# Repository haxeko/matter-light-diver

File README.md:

# matter-light-diver – Driver đèn CCT 3 dây, ESP32‑C6, Matter over Thread

Thiết kế hoàn chỉnh (tài liệu, sơ đồ nguyên lý, tính toán, floorplan PCB, BOM, firmware) cho **driver đèn LED điều chỉnh nhiệt độ màu loại 3 dây** (V+ chung, CW–, WW–) điều khiển bằng **ESP32‑C6** qua **Matter over Thread**, có **nguồn flyback cách ly** bên trong và **3 nút gạt chọn công suất**. Kiến trúc theo kiểu driver đèn thông minh thương mại: flyback CC/CV + MCU ở phía thứ cấp (SELV) + chuyển kênh CW/WW bằng PWM bù nhau.

| Thông số | Giá trị |
|---|---|
| Vào | 176–264 VAC |
| Ra | 20–42 V, 250–950 mA (8 mức DIP), 40 W max; bản 20 W cho PCB 30 × 60 mm |
| Điều khiển | Matter 1.x – Color Temperature Light, Thread FTD, commissioning BLE |
| Điều sáng | 1–100 % analog CC (12 bit), không nhấp nháy; CCT 2700–6500 K |
| Cách ly | tăng cường 3.75 kV, creepage ≥ 8 mm, opto 5 kV, tụ Y1 |
| PCB | KiCad 30 × 95 mm (40 W), 2 lớp, THT mặt trên / SMD mặt dưới; biến thể 30 × 60–65 mm (≤ 20 W) |

## Cấu trúc kho

```
docs/                      tài liệu thiết kế (tiếng Việt)
  01-tong-quan-kien-truc.md      yêu cầu, kiến trúc, bảng DIP
  02-nguon-cach-ly-flyback.md    tính toán flyback, biến áp, linh kiện sơ cấp
  03-thu-cap-cc-cv-dieu-sang.md  vòng CC/CV, PWM→DAC, chuyển kênh CW/WW, nguồn phụ
  04-mcu-esp32c6.md              GPIO, nạp/debug, anten
  05-pcb-layout.md               floorplan, khoảng cách an toàn, nhiệt
  06-firmware.md                 kiến trúc firmware, thuật toán, build, commissioning
  07-kiem-thu-an-toan.md         bring-up, kiểm thử, an toàn, EMC
  bom/BOM.csv                    danh mục linh kiện (có mã thay thế LCSC)
  images/block_diagram.svg       sơ đồ khối (sinh bởi gen_block_diagram.py)
hardware/
  kicad/                         DỰ ÁN KICAD (schematic + PCB 30x95 mm, Gerber, DSN) sinh từ design_db.py
  calc/flyback_calc.py           tính toán flyback (in bảng Markdown / JSON)
  calc/secondary_calc.py         bảng DIP, vòng CC, kẹp CV, MOSFET, nguồn phụ
  schematics/0X_*.svg            sơ đồ nguyên lý 7 khối (sinh bởi gen_0X_*.py, schemdraw)
  pcb/floorplan_30x90.svg        floorplan PCB (sinh bởi gen_floorplan.py)
firmware/                        dự án ESP-IDF 5.2 + esp-matter 1.3/1.4 (ESP32-C6)
  main/app_main.cpp              node Matter, endpoint 0x010C, OpenThread
  main/app_driver.cpp            LEDC/ADC/GPIO/nút/LED, tick 10 ms, bảo vệ
  main/light_engine.c            toán học điều sáng/CCT (thuần C)
  main/board_config.h            bản đồ chân, hằng số phần cứng
  test_host/                     unit test chạy bằng gcc
```

## Sơ đồ nguyên lý

| Khối | Tệp |
|---|---|
| 1 – Đầu vào AC, lọc EMI, chỉnh lưu | `hardware/schematics/01_input_filter.svg` |
| 2 – Flyback: T1 PQ20/20, Q1, clamp, cuộn phụ, chỉnh lưu thứ cấp | `02_flyback_stage.svg` |
| 3 – UCC28740, VS, HV start‑up, opto, tụ Y | `03_controller.svg` |
| 4 – Khuếch đại dòng, bộ lỗi CC, TL431 CV, tham chiếu PWM→DAC, ADC | `04_cc_cv_loop.svg` |
| 5 – Dịch mức, MOSFET CW/WW, shunt, đầu ra 3 dây | `05_output_switch.svg` |
| 6 – Buck 5 V, LDO 3.3 V | `06_aux_supply.svg` |
| 7 – ESP32‑C6‑MINI‑1, DIP, nút, LED, NTC, USB/UART | `07_mcu.svg` |

Sinh lại hình/tính toán (cần `pip install schemdraw`):

```bash
python3 hardware/calc/flyback_calc.py
python3 hardware/calc/secondary_calc.py
for f in hardware/schematics/gen_*.py docs/images/gen_block_diagram.py hardware/pcb/gen_floorplan.py; do python3 "$f"; done
```

## PCB KiCad

`hardware/kicad/` chứa project KiCad 7 (mở được bằng 7/8/9): `matter_cct_driver.kicad_pcb` (đặt linh kiện xong, đi dây tự động ≈ 70 % kết nối (160/230), phần đã đi sạch DRC; phần còn lại hoàn thiện tay hoặc Freerouting), schematic kết nối, thư viện footprint riêng (ESP32‑C6‑MINI‑1, PQ20/20, UU9.8…), Gerber/drill, PDF/SVG hai mặt và file DSN cho Freerouting. Toàn bộ được sinh từ `hardware/kicad/design_db.py` bằng API `pcbnew`; xem `hardware/kicad/README.md`.

## Firmware

```bash
. $IDF_PATH/export.sh && . $ESP_MATTER_PATH/export.sh
cd firmware && idf.py set-target esp32c6 && idf.py build flash monitor
# unit test logic điều sáng trên máy tính
cd firmware/test_host && cc -std=c11 -I../main test_light_engine.c ../main/light_engine.c -lm -o test && ./test
```

Firmware viết theo API esp‑matter v1.3/v1.4 + ESP‑IDF 5.2; `light_engine` đã được kiểm thử trên máy, phần còn lại chưa biên dịch trong môi trường này (không có toolchain ESP‑IDF) – xem `docs/06-firmware.md`.

## Cảnh báo an toàn

Phía sơ cấp mang điện áp lưới. Chỉ bring‑up qua biến áp cách ly/variac, không nối USB khi board đang cắm điện lưới, tuân thủ khoảng cách cách ly trong `docs/05`. Bản 40 W bán thương mại cần thêm PFC để đạt IEC 61000‑3‑2 lớp C (xem `docs/07`).

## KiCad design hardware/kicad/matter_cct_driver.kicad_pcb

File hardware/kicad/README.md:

# Dự án KiCad – driver đèn CCT 3 dây (ESP32‑C6, Matter over Thread)

Thư mục này là dự án **KiCad 7** (mở được bằng KiCad 7/8/9) được **sinh hoàn toàn bằng script** từ một cơ sở dữ liệu thiết kế duy nhất (`design_db.py`), vì vậy schematic, PCB, BOM luôn nhất quán.

| Tệp | Nội dung |
|---|---|
| `matter_cct_driver.kicad_pro` | Project (net class: AC 0.8 mm/1.0 mm; HV 0.8/0.6; PWR_S 1.0/0.3; PWR_L 0.5/0.2; SIG 0.25/0.2) |
| `matter_cct_driver.kicad_pcb` | PCB 30 × 95 mm, 2 lớp, 99 footprint, 64 net, đã đặt linh kiện + đi dây tự động (xem trạng thái bên dưới) |
| `matter_cct_driver.kicad_sch` | Schematic kiểu "kết nối" (mỗi chân gắn global label) – dùng để kiểm tra ERC/netlist và cập nhật PCB; sơ đồ nguyên lý dễ đọc ở `../schematics/*.svg` |
| `lib/driver.pretty`, `lib/driver.kicad_sym` | Footprint/symbol riêng: ESP32‑C6‑MINI‑1 (chuyển từ thư viện KiCad mới), biến áp PQ20/20, cuộn UU9.8, pad hàn dây, fuse 2410… |
| `design_db.py` | **Nguồn sự thật**: linh kiện, footprint, net, vị trí/vùng đặt, lớp net, keepout |
| `gen_kicad_pcb.py` | Sinh PCB bằng API `pcbnew`: nạp footprint, gán net, đặt (cố định + đóng gói tự động theo vùng), viền, rãnh phay, rule area, vùng đồng GND, đi dây, DRC |
| `router.py` | Router lưới 2 lớp tự viết (A*, 0.125 mm, neck‑down tại pad, via stub GND, thu hẹp bề rộng khi nghẽn) |
| `gen_kicad_sch.py` | Sinh schematic + thư viện symbol (netlist đã đối chiếu trùng với PCB) |
| `fix_gnd_stubs.py` | Sau khi đi dây: thử đặt via stub cho các pad GND còn hở, giữ lại khi DRC sạch và số kết nối thiếu giảm |
| `make_footprints.py`, `inspect_footprints.py` | Tạo footprint riêng, in kích thước courtyard |
| `output/` | Gerber + drill, PDF/SVG hai mặt, `schematic.pdf`, `netlist.xml`, `matter_cct_driver.dsn` (Specctra, cho Freerouting), `drc_report.txt` |

## Trạng thái thiết kế

* Bố trí: THT lớn (J1, L1, RV1, RT1, CX1, C1/C27, T1, C4, CY1, J2/J4, module ESP32‑C6) ở **mặt trên**; SMD nhỏ (0402, SOT, SMA, UCC28740, op‑amp…) ở **mặt dưới** – đúng kiểu driver thương mại.
* Cách ly: hàng rào thẳng x = 45 mm giữa biến áp, rule area cấm đồng ±0.6 mm; opto SO‑4 thân rộng (10.3 mm) ở mặt dưới ngay dưới biến áp; tụ Y1 pitch 10 mm + rãnh phay 1 mm; vùng đồng GND_P / GND_S tách biệt hai bên; keepout anten (không đồng dưới phần anten module, phần lõi module không đi track lớp trên).
* Đi dây: router tự động + via stub GND nối được **160/230 kết nối (≈ 70 %)** – 1 316 đoạn, 119 via; phần đã đi **không có vi phạm DRC** (clearance, keepout, lỗ–lỗ, cạnh board) – chỉ còn cảnh báo silk và 70 cặp chân chưa nối (`output/drc_report.txt`, mục *unconnected*). Chưa nối chủ yếu là GND_S ở vùng SMD dày (22 – cần via stitching/thu hẹp vùng đồng), nguồn thứ cấp (VPLUS, SENSE_P, CW_N/WW_N, +5V/+3V3) và vài tín hiệu quanh module – nên **hoàn thiện bằng tay trong KiCad** (ratsnest đã có) hoặc dùng Freerouting: *File → Export → Specctra DSN* (hoặc dùng `output/matter_cct_driver.dsn`), chạy `java -jar freerouting-x.jar -de board.dsn -do board.ses`, rồi *File → Import → Specctra Session*. (Môi trường tạo thiết kế này không được phép chạy Freerouting nên bước đó để lại cho người dùng.)
* Chưa làm: mô hình 3D, tối ưu nhiệt (đổ đồng tản nhiệt Q1/D2 đã có qua vùng GND nhưng cần thêm via nhiệt), kiểm tra creepage bằng rule tuỳ chỉnh của KiCad 8 (`(rule ... (condition "A.NetClass == 'HV'"))`).

## Sinh lại

```bash
sudo apt install kicad kicad-symbols kicad-footprints     # KiCad 7 (hoặc 8/9 – chỉnh API pcbnew nếu cần)
pip install kiutils numpy
cd hardware/kicad
python3 make_footprints.py            # lib/driver.pretty
python3 gen_kicad_pcb.py --route      # PCB + DRC (bỏ --route để chỉ đặt linh kiện)
python3 fix_gnd_stubs.py              # via stub cho pad GND còn hở (tuỳ chọn)
python3 gen_kicad_sch.py              # schematic
kicad-cli sch export netlist --format kicadxml -o output/netlist.xml matter_cct_driver.kicad_sch
kicad-cli pcb export gerbers -o output/gerber/ matter_cct_driver.kicad_pcb
```

Thay đổi thiết kế (giá trị, footprint, vị trí, vùng, net class) chỉ cần sửa `design_db.py` rồi chạy lại.

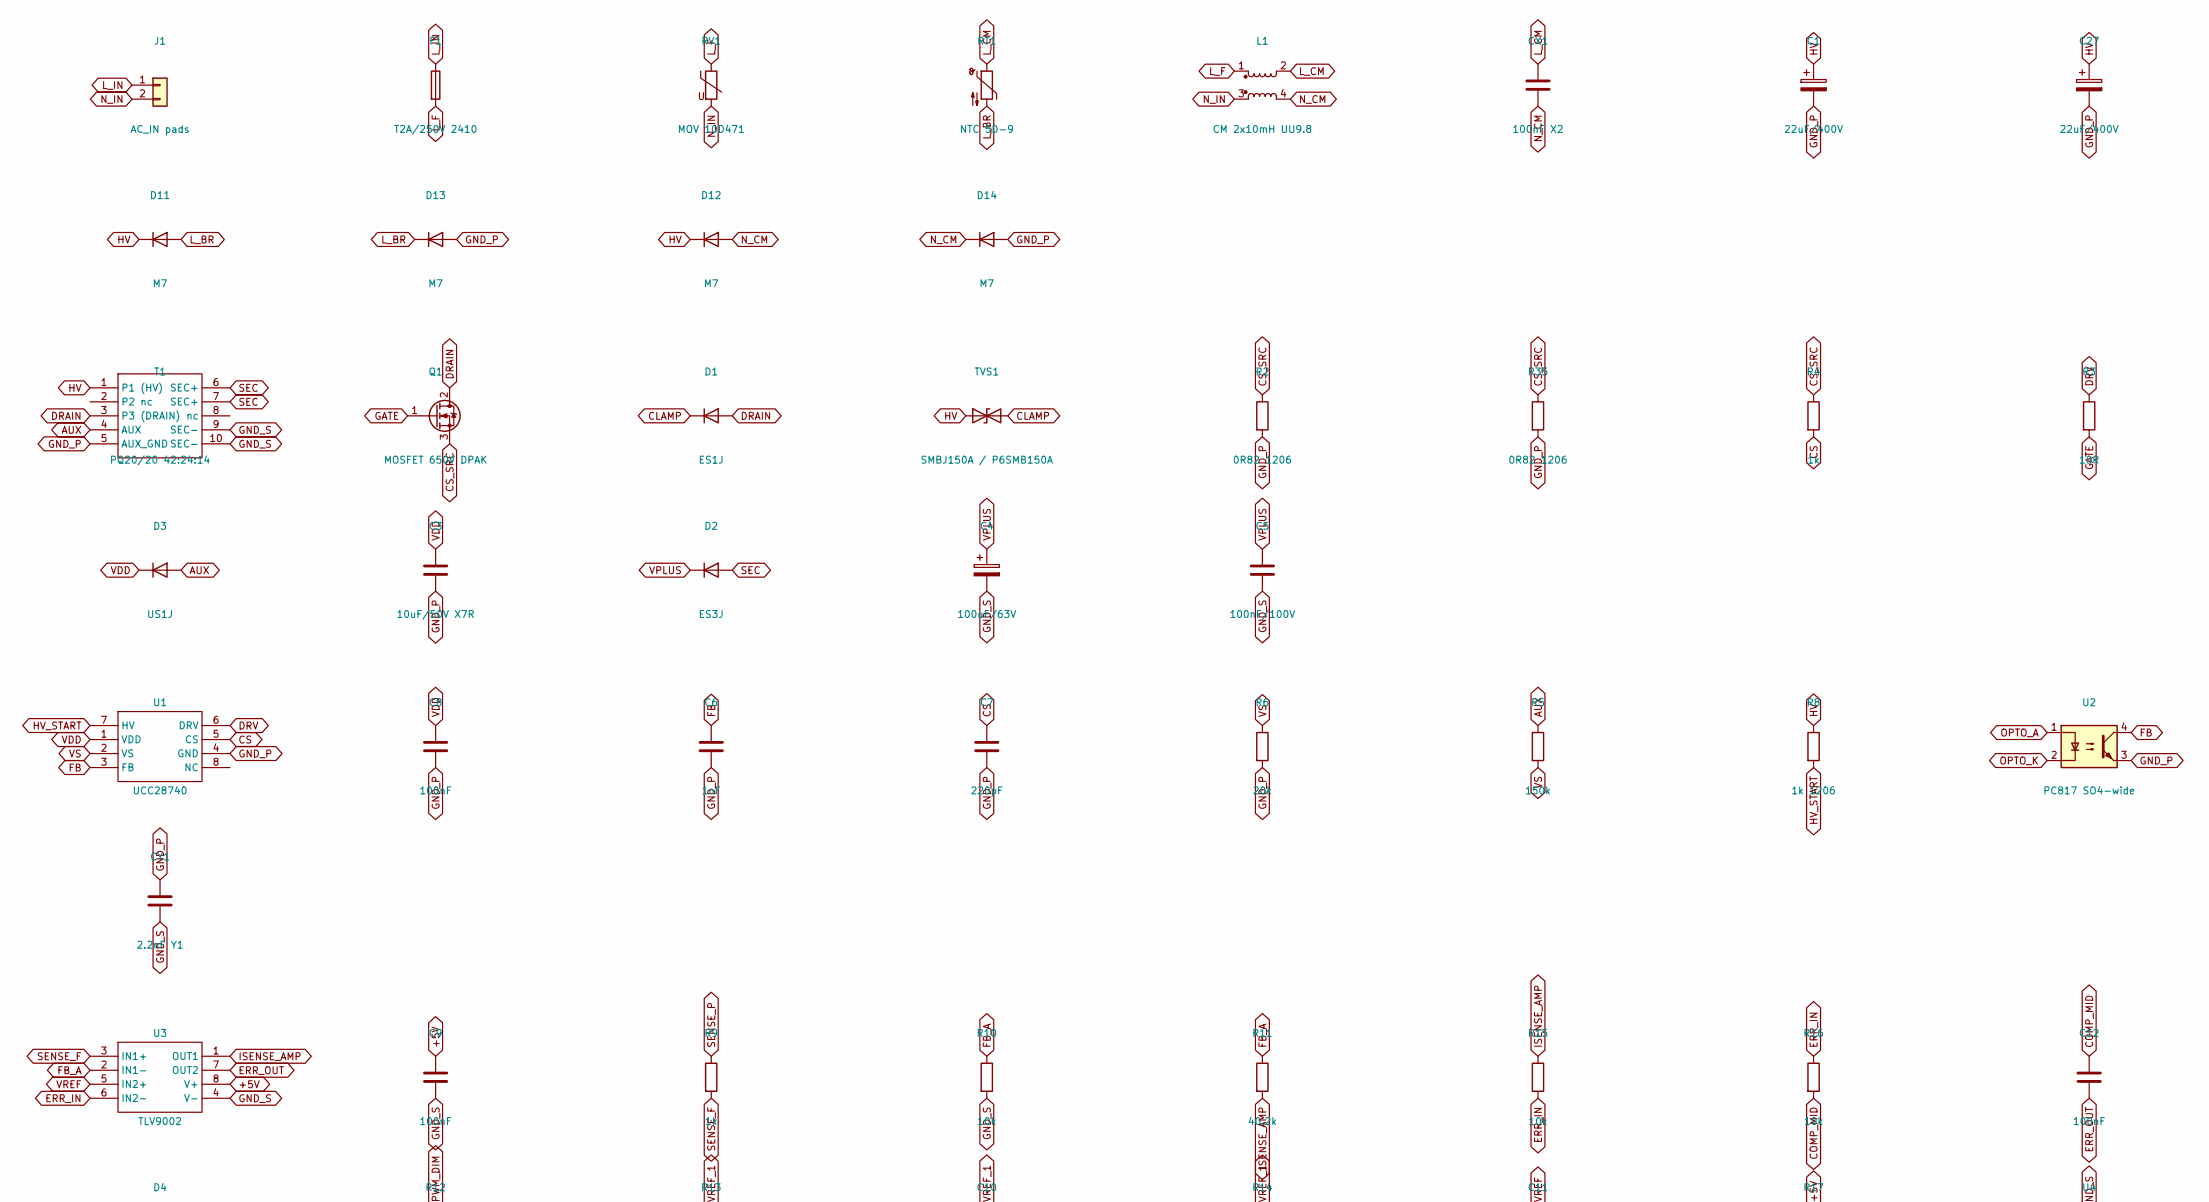
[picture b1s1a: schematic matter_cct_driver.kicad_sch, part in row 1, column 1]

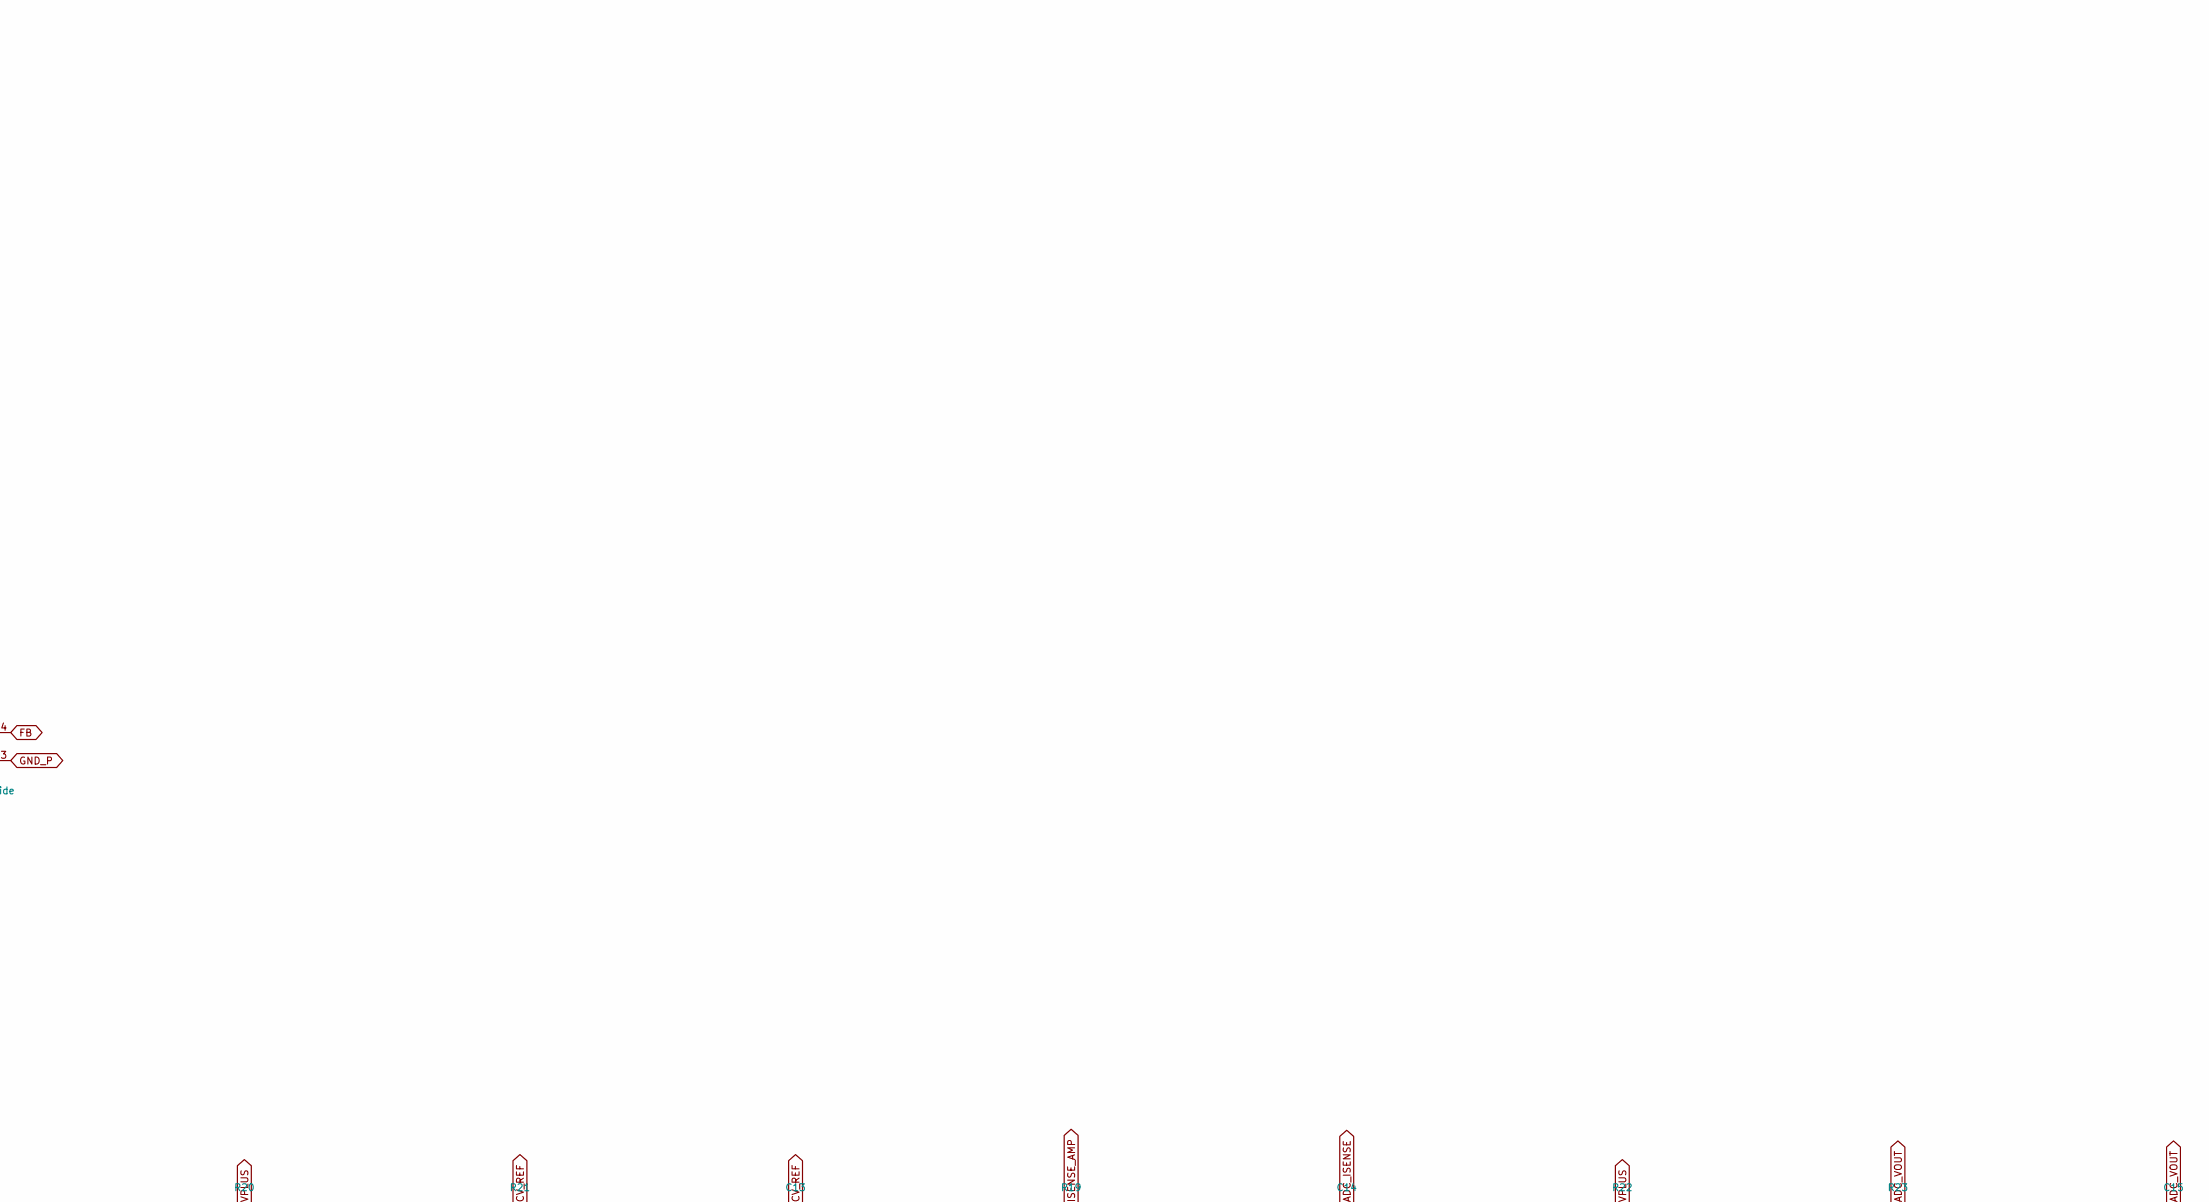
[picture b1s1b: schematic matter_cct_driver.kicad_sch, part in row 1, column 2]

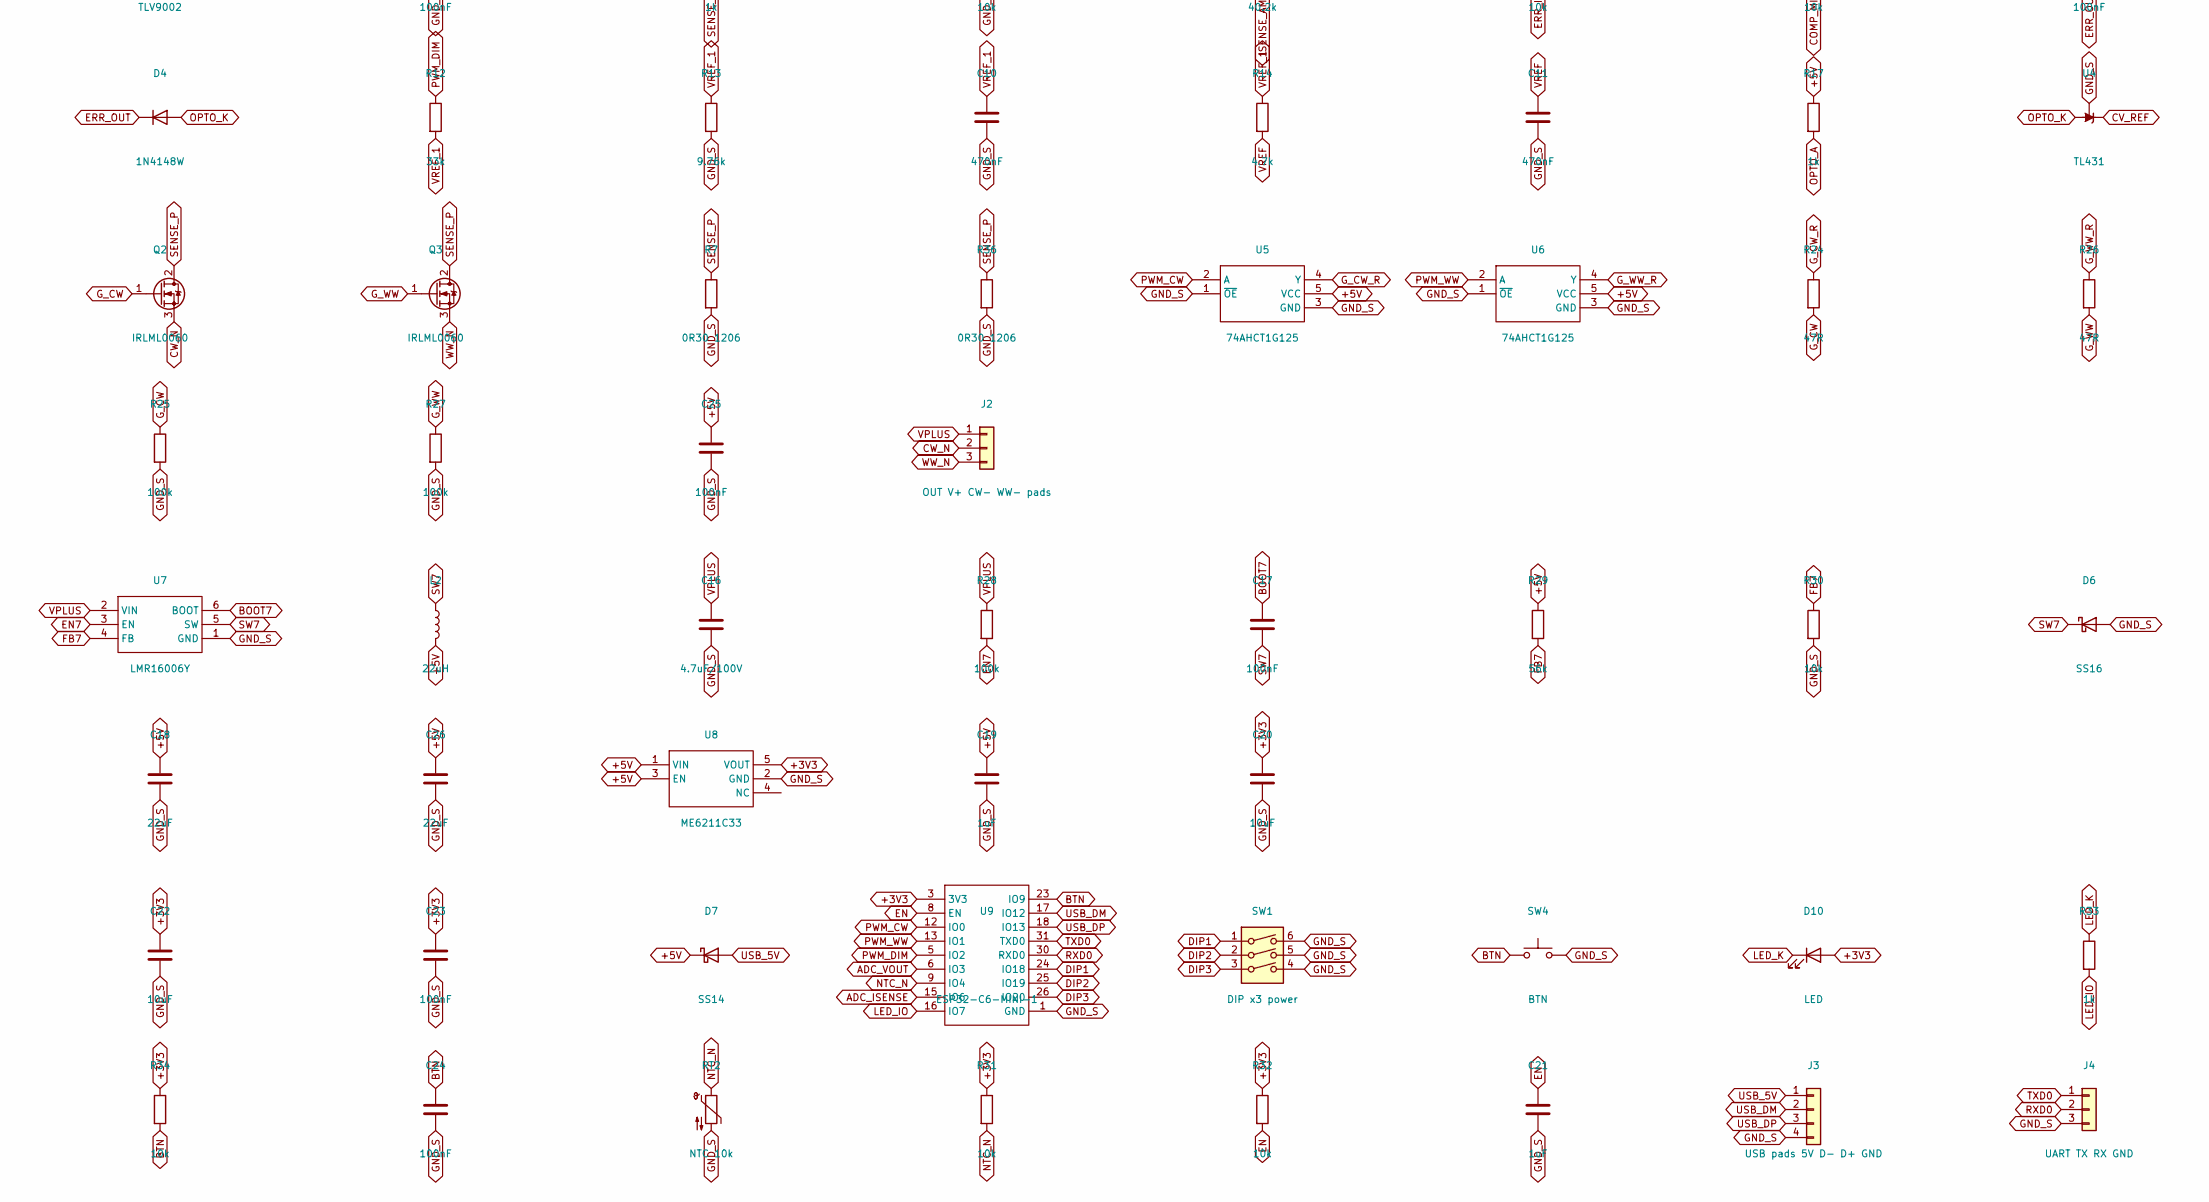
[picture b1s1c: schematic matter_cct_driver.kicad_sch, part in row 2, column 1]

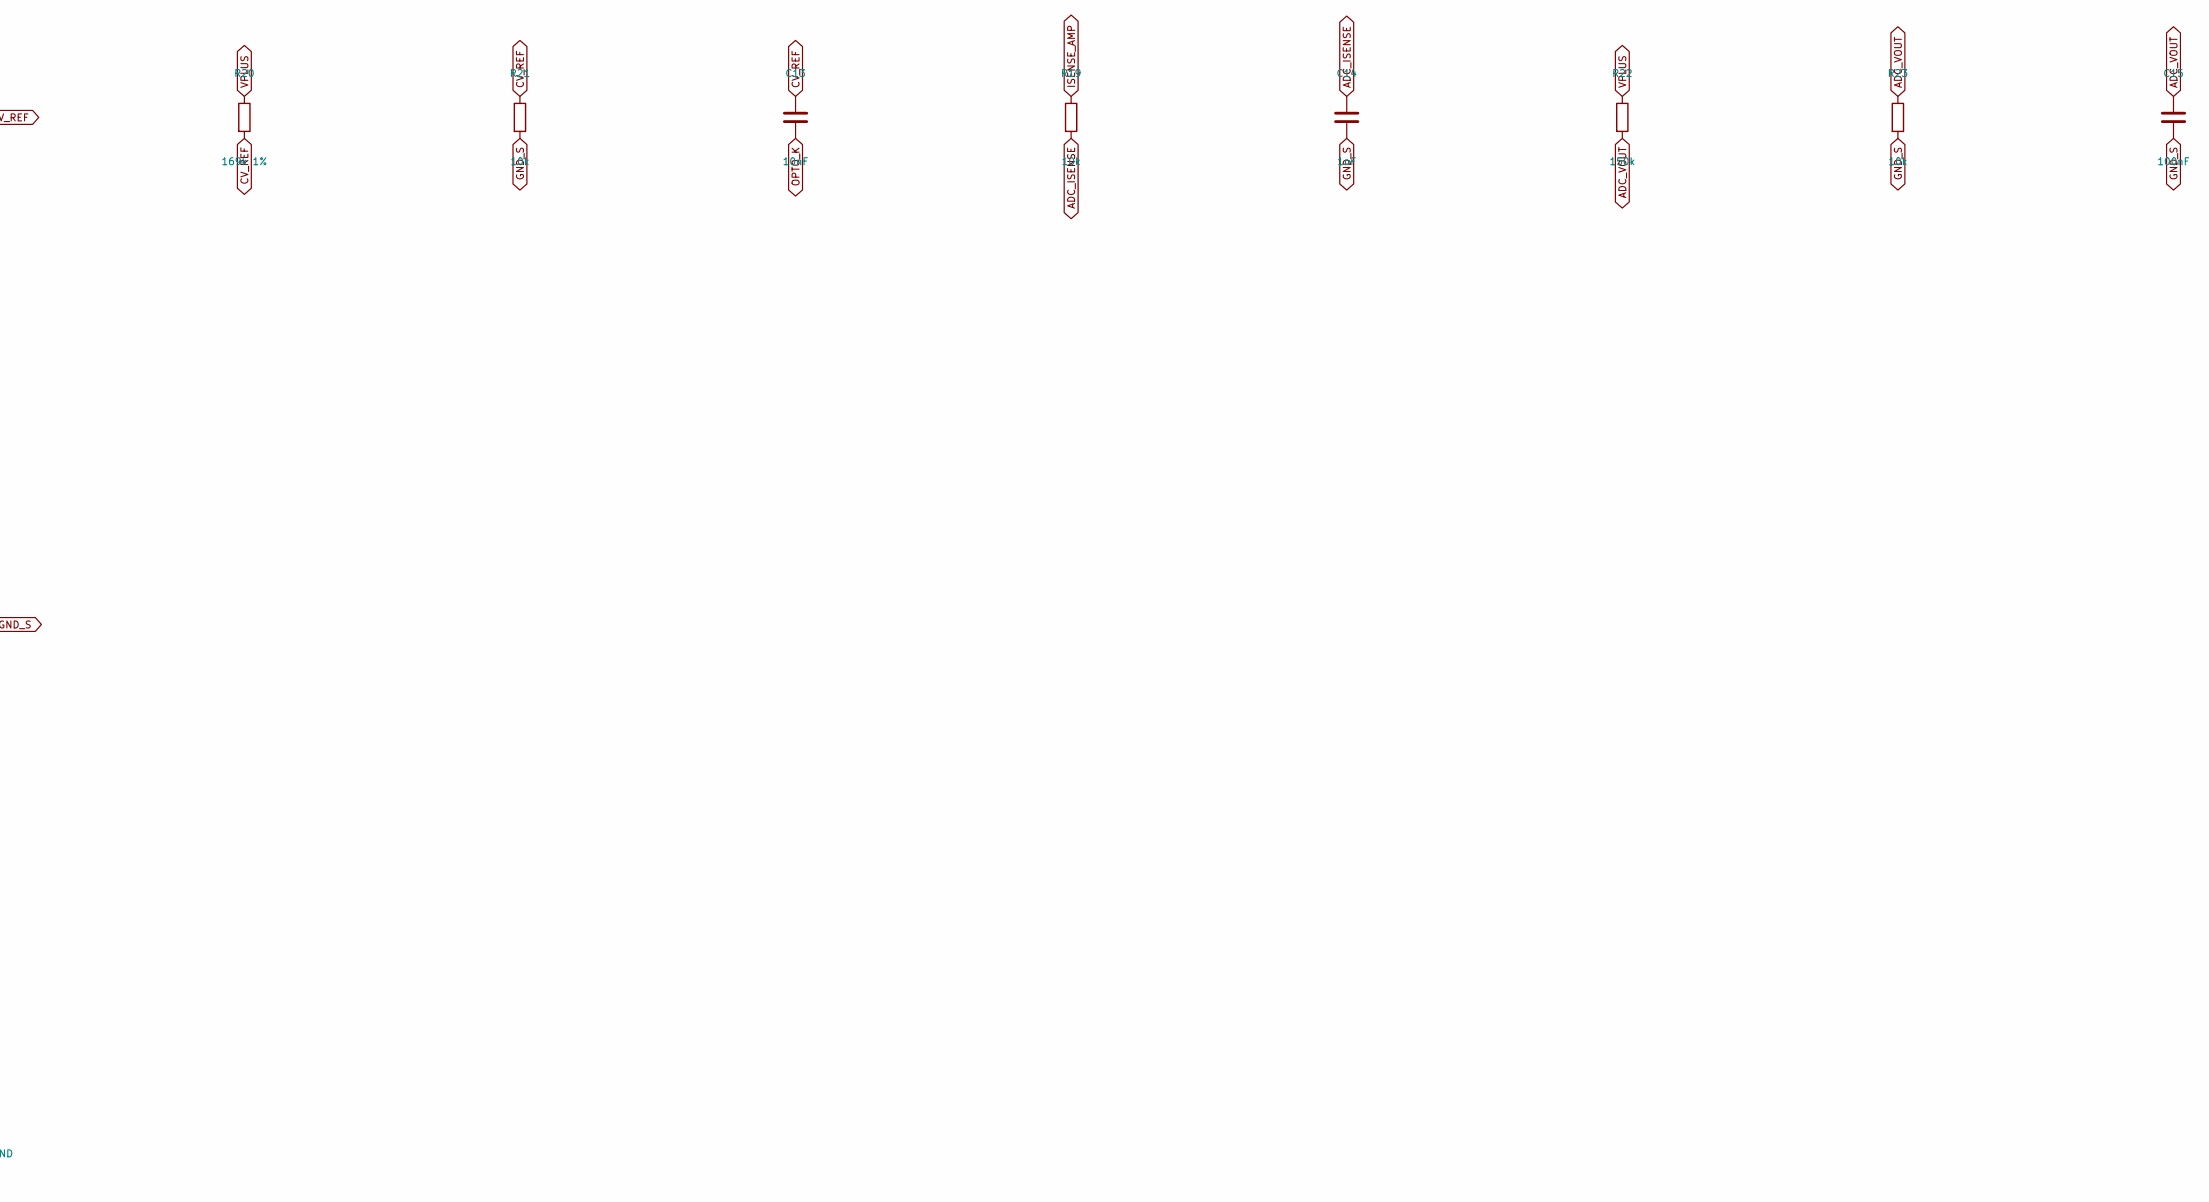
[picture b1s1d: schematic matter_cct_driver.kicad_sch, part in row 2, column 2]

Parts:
C1, C27: 22uF/400V; CP_Radial_D10.0mm_P5.00mm
C3: 10uF/50V X7R; C_1206_3216Metric
C4: 100uF/63V; CP_Radial_D8.0mm_P3.50mm
C5: 100nF/100V; C_0805_2012Metric
C6, C14: 1nF; C_0402_1005Metric
C7: 220pF; C_0402_1005Metric
C8, C9, C12, C15, C17, C23, C24, C25: 100nF; C_0402_1005Metric
C10, C11: 470nF; C_0402_1005Metric
C13: 10nF; C_0402_1005Metric
C16: 4.7uF/100V; C_1210_3225Metric
C18, C26: 22uF; C_0805_2012Metric
C19, C21: 1uF; C_0402_1005Metric
C20, C22: 10uF; C_0805_2012Metric
CX1: 100nF X2; C_Rect_L13.0mm_W5.0mm_P10.00mm_FKS3_FKP3_MKS4
CY1: 2.2nF Y1; C_Disc_D8.0mm_W5.0mm_P10.00mm
D1: ES1J; D_SMA
D2: ES3J; D_SMC
D3: US1J; D_SMA
D4: 1N4148W; D_SOD-123
D6: SS16; D_SMA
D7: SS14; D_SMA
D10: LED; LED_0805_2012Metric
D11, D12, D13, D14: M7; D_SMA
F1: T2A/250V 2410; Fuse_2410_6032Metric
J1: AC_IN pads; WirePads_1x02_P5.08mm
J2: OUT V+ CW- WW- pads; WirePads_1x03_P3.81mm
J3: USB pads 5V D- D+ GND; Pads_1x04_P2.54mm
J4: UART TX RX GND; PinHeader_1x03_P2.54mm_Vertical
L1: CM 2x10mH UU9.8; CM_Choke_UU9.8
L2: 22uH; L_Bourns_SRN6045TA
Q1: MOSFET 650V DPAK; TO-252-2
Q2, Q3: IRLML0060; SOT-23
R2, R35: 0R82 1206; R_1206_3216Metric
R3: 10R; R_0402_1005Metric
R4, R9, R17, R33: 1k; R_0402_1005Metric
R5, R22: 150k; R_0402_1005Metric
R6: 20k; R_0402_1005Metric
R7, R36: 0R30 1206; R_1206_3216Metric
R8: 1k 1206; R_1206_3216Metric
R10, R15, R16, R19, R21, R23, R30, R31, R32, R34: 10k; R_0402_1005Metric
R11: 40.2k; R_0402_1005Metric
R12: 33k; R_0402_1005Metric
R13: 9.76k; R_0402_1005Metric
R14: 4.7k; R_0402_1005Metric
R20: 169k 1%; R_0402_1005Metric
R24, R26: 47R; R_0402_1005Metric
R25, R27, R28: 100k; R_0402_1005Metric
R29: 56k; R_0402_1005Metric
RT1: NTC 5D-9; C_Disc_D9.0mm_W5.0mm_P5.00mm
RT2: NTC 10k; R_0402_1005Metric
RV1: MOV 10D471; C_Disc_D10.5mm_W5.0mm_P7.50mm
SW1: DIP x3 power; SW_DIP_SPSTx03_Slide_6.7x9.18mm_W8.61mm_P2.54mm_LowProfile
SW4: BTN; SW_SPST_SKQG_WithoutStem
T1: PQ20/20 42:24:14; Transformer_PQ20-20_5+5
TVS1: SMBJ150A / P6SMB150A; D_SMB
U1: UCC28740; SOIC-8_3.9x4.9mm_P1.27mm
U2: PC817 SO4-wide; SO-4_7.6x3.6mm_P2.54mm
U3: TLV9002; SOIC-8_3.9x4.9mm_P1.27mm
U4: TL431; SOT-23
U5, U6: 74AHCT1G125; SOT-353_SC-70-5
U7: LMR16006Y; SOT-23-6
U8: ME6211C33; SOT-23-5
U9: ESP32-C6-MINI-1

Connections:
+3V3: C20.1, C22.1, C23.1, D10.2 (A), R31.1, R32.1, R34.1, U8.5 (VOUT), U9.3 (3V3)
+5V: C9.1, C18.1, C19.1, C25.1, C26.1, D7.1 (K), L2.2, R17.1, R29.1, U3.8 (V+), U5.5 (VCC), U6.5 (VCC), U8.1 (VIN), U8.3 (EN)
ADC_ISENSE: C14.1, R19.2, U9.15 (IO6)
ADC_VOUT: C15.1, R22.2, R23.1, U9.6 (IO3)
AUX: D3.2 (A), R5.1, T1.4 (AUX)
BOOT7: C17.1, U7.6 (BOOT)
BTN: C24.1, R34.2, SW4.1, U9.23 (IO9)
CLAMP: D1.1 (K), TVS1.2 (A2)
COMP_MID: C12.1, R16.2
CS: C7.1, R4.2, U1.5 (CS)
CS_SRC: Q1.3 (S), R2.1, R4.1, R35.1
CV_REF: C13.1, R20.2, R21.1, U4.1 (K)
CW_N: J2.2, Q2.3 (S)
DIP1: SW1.1, U9.24 (IO18)
DIP2: SW1.2, U9.25 (IO19)
DIP3: SW1.3, U9.26 (IO20)
DRAIN: D1.2 (A), Q1.2 (D), T1.3 (P3 (DRAIN))
DRV: R3.1, U1.6 (DRV)
EN: C21.1, R32.2, U9.8 (EN)
EN7: R28.2, U7.3 (EN)
ERR_IN: R15.2, R16.1, U3.6 (IN2-)
ERR_OUT: C12.2, D4.1 (K), U3.7 (OUT2)
FB: C6.1, U1.3 (FB), U2.4
FB7: R29.2, R30.1, U7.4 (FB)
FB_A: R10.1, R11.1, U3.2 (IN1-)
GATE: Q1.1 (G), R3.2
GND_P: C1.2, C3.2, C6.2, C7.2, C8.2, C27.2, CY1.1, D13.2 (A), D14.2 (A), R2.2, R6.2, R35.2, T1.5 (AUX_GND), U1.4 (GND), U2.3
GND_S: C4.2, C5.2, C9.2, C10.2, C11.2, C14.2, C15.2, C16.2, C18.2, C19.2, C20.2, C21.2, C22.2, C23.2, C24.2, C25.2, C26.2, CY1.2, D6.2 (A), J3.4, J4.3, R7.2, R10.2, R13.2, R21.2, R23.2, R25.2, R27.2, R30.2, R36.2, RT2.2, SW1.4, SW1.5, SW1.6, SW4.2, T1.9 (SEC-), T1.10 (SEC-), U3.4 (V-), U4.2 (REF), U5.1 (~OE), U5.3 (GND), U6.1 (~OE), U6.3 (GND), U7.1 (GND), U8.2 (GND), U9.1 (GND), U9.2 (GND), U9.11 (GND), U9.14 (GND), U9.36 (GND), U9.37 (GND), U9.38 (GND), U9.39 (GND), U9.40 (GND), U9.41 (GND), U9.42 (GND), U9.43 (GND), U9.44 (GND), U9.45 (GND), U9.46 (GND), U9.47 (GND), U9.48 (GND), U9.49 (GND), U9.50 (GND), U9.51 (GND), U9.52 (GND), U9.53 (GND)
G_CW: Q2.1 (G), R24.2, R25.1
G_CW_R: R24.1, U5.4 (Y)
G_WW: Q3.1 (G), R26.2, R27.1
G_WW_R: R26.1, U6.4 (Y)
HV: C1.1, C27.1, D11.1 (K), D12.1 (K), R8.1, T1.1 (P1 (HV)), TVS1.1 (A1)
HV_START: R8.2, U1.7 (HV)
ISENSE_AMP: R11.2, R15.1, R19.1, U3.1 (OUT1)
LED_IO: R33.2, U9.16 (IO7)
LED_K: D10.1 (K), R33.1
L_BR: D11.2 (A), D13.1 (K), RT1.2
L_CM: CX1.1, L1.2, RT1.1
L_F: F1.2, L1.1, RV1.1
L_IN: F1.1, J1.1
NTC_N: R31.2, RT2.1, U9.9 (IO4)
N_CM: CX1.2, D12.2 (A), D14.1 (K), L1.4
N_IN: J1.2, L1.3, RV1.2
OPTO_A: R17.2, U2.1
OPTO_K: C13.2, D4.2 (A), U2.2, U4.3 (A)
PWM_CW: U5.2 (A), U9.12 (IO0)
PWM_DIM: R12.1, U9.5 (IO2)
PWM_WW: U6.2 (A), U9.13 (IO1)
RXD0: J4.2, U9.30 (RXD0)
SEC: D2.2 (A), T1.6 (SEC+), T1.7 (SEC+)
SENSE_F: R9.2, U3.3 (IN1+)
SENSE_P: Q2.2 (D), Q3.2 (D), R7.1, R9.1, R36.1
SW7: C17.2, D6.1 (K), L2.1, U7.5 (SW)
TXD0: J4.1, U9.31 (TXD0)
USB_5V: D7.2 (A), J3.1
USB_DM: J3.2, U9.17 (IO12)
USB_DP: J3.3, U9.18 (IO13)
VDD: C3.1, C8.1, D3.1 (K), U1.1 (VDD)
VPLUS: C4.1, C5.1, C16.1, D2.1 (K), J2.1, R20.1, R22.1, R28.1, U7.2 (VIN)
VREF: C11.1, R14.2, U3.5 (IN2+)
VREF_1: C10.1, R12.2, R13.1, R14.1
VS: R5.2, R6.1, U1.2 (VS)
WW_N: J2.3, Q3.3 (S)

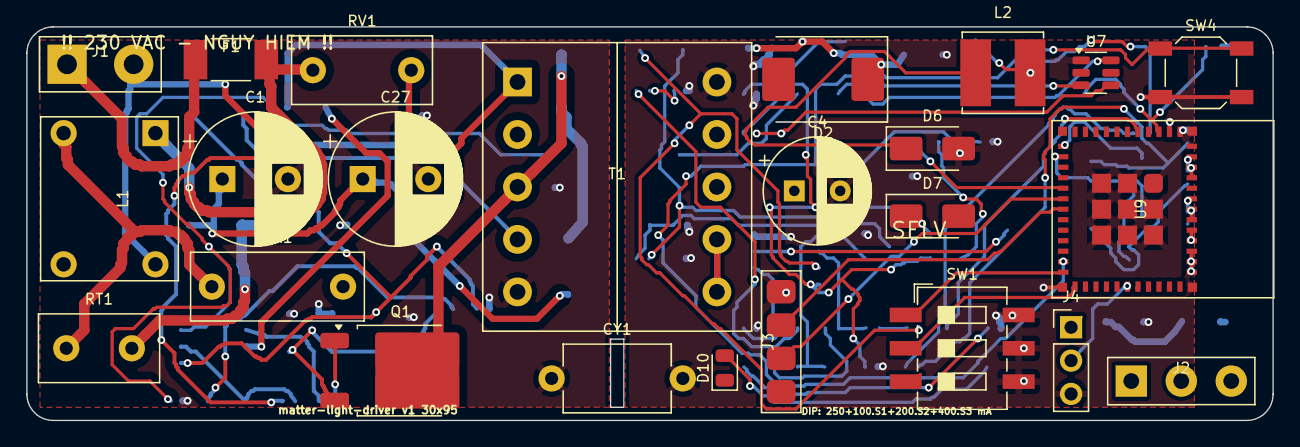
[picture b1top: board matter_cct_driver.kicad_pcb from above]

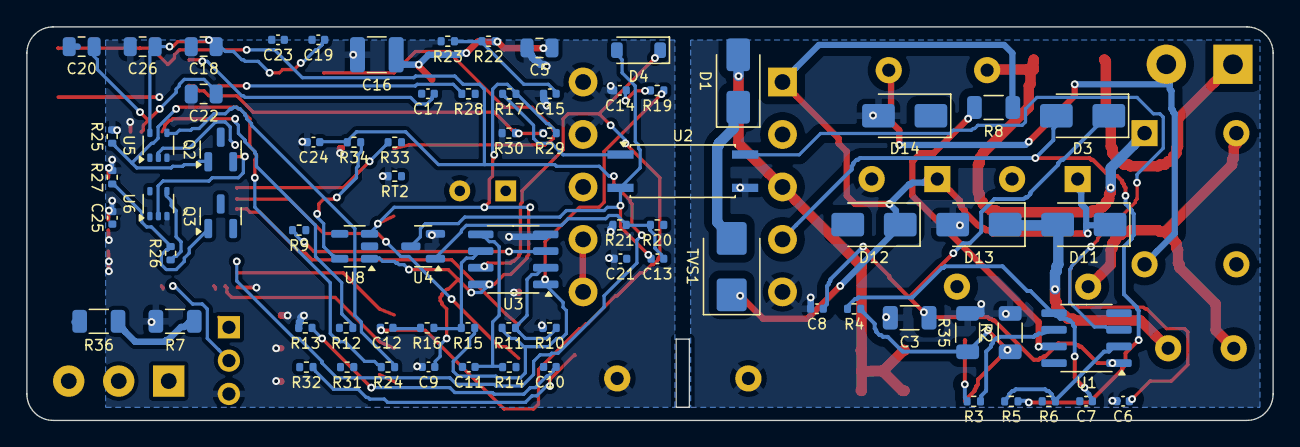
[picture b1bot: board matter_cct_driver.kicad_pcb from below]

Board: 2 copper layers, 95.0 x 30.0 mm, 99 parts (75 on the bottom side), 64 nets.

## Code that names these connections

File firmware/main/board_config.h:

/*
 * board_config.h - Hardware mapping for the 3-wire CCT LED driver (ESP32-C6, Matter over Thread).
 *
 * Every number here mirrors the hardware documented in docs/03 and docs/04.
 * Change the DIP table / scaling constants here if the shunt, gain or divider change.
 */
#pragma once

/* ---------------------------------------------------------------- GPIO map */
#define PIN_PWM_CW        0     /* LEDC ch0  -> U5 -> Q2 (cool white low-side switch)  */
#define PIN_PWM_WW        1     /* LEDC ch1  -> U6 -> Q3 (warm white low-side switch)  */
#define PIN_PWM_DIM       2     /* LEDC ch2  -> RC filter -> current reference (VREF)  */
#define PIN_ADC_VOUT      3     /* ADC1_CH3  <- V+ via 150k/10k                        */
#define PIN_ADC_NTC       4     /* ADC1_CH4  <- 10k / NTC 10k B3950                    */
#define PIN_ADC_ISENSE    6     /* ADC1_CH6  <- ISENSE_AMP (0.753 V = 1.0 A)           */
#define PIN_BUTTON        9     /* active low, 10k pull-up, also BOOT strapping pin    */
#define PIN_STATUS_LED    7     /* active low (IO10 is not bonded out on ESP32-C6-MINI-1) */
#define PIN_DIP1          18    /* active low (switch to GND), internal pull-up        */
#define PIN_DIP2          19
#define PIN_DIP3          20

#define ADC_CH_VOUT       3
#define ADC_CH_NTC        4
#define ADC_CH_ISENSE     6

/* ---------------------------------------------------------------- LEDC */
#define DIM_PWM_FREQ_HZ   19531   /* 80 MHz / 2^12                                     */
#define DIM_PWM_RES_BITS  12
#define CH_PWM_FREQ_HZ    4000    /* CW/WW complementary switching                     */
#define CH_PWM_RES_BITS   13      /* 8192 counts per period (80 MHz / 8192 = 9.7 kHz max) */
#define CH_OVERLAP_US     2       /* make-before-break overlap at the CW->WW edge      */

/* ---------------------------------------------------------------- current scaling
 * VREF(100 % duty) = 3.3 V * 9.76k/(33k+9.76k) = 0.753 V
 * I = VREF / (gain * Rsense) = 0.753 / (5.02 * 0.15) = 1.000 A  -> duty = I_mA / 1000
 */
#define I_HW_MAX_MA       1000    /* hardware clamp, do not raise without changing R12/R13 */
#define I_MIN_MA          10      /* lowest controllable current (1 %)                 */
#define DIP_CURRENT_TABLE_MA { 250, 350, 450, 550, 650, 750, 850, 950 }  /* index = S3S2S1 */

/* ---------------------------------------------------------------- colour */
#define CCT_MIN_MIREDS    153     /* 6500 K */
#define CCT_MAX_MIREDS    370     /* 2700 K */
#define CCT_DEFAULT_MIREDS 250    /* 4000 K */

/* ---------------------------------------------------------------- behaviour */
#define SOFT_CONNECT_MS   40      /* ramp of the channel duty when switching on from CV mode */
#define FADE_DEFAULT_MS   250     /* local smoothing of level / colour steps            */
#define ENGINE_TICK_MS    10
#define DIP_POLL_MS       100
#define DIP_DEBOUNCE_TICKS 5      /* 500 ms stable before applying a new power setting */

/* ---------------------------------------------------------------- protection */
#define VOUT_DIVIDER_RATIO 16.0f  /* (150k + 10k) / 10k                                 */
#define VOUT_OPEN_LOAD_V   44.0f  /* V+ still at CV clamp while ON  -> no lamp         */
#define VOUT_SHORT_V       8.0f   /* V+ collapsed while current flows -> short circuit */
#define FAULT_RETRY_MS     5000
#define NTC_DERATE_C       85
#define NTC_SHUTDOWN_C     100
#define NTC_R25_OHM        10000.0f
#define NTC_BETA           3950.0f
#define NTC_PULLUP_OHM     10000.0f
